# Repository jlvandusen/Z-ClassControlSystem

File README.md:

# Z-Class Control System — BB-8 firmware fleet + tooling

Firmware, build system, and a full serial mission-control CLI for the
[Z-Class BB-8 drive system](https://github.com/jlvandusen/Z-ClassDriveSystem).
**This repo is primary for all control and software supporting that drive**; the
hardware half — mechanics/STLs, PCB fabrication files, BOM, wiring docs — lives in
[Z-ClassDriveSystem](https://github.com/jlvandusen/Z-ClassDriveSystem).

VERSION 10 upcoming board

RC4 is a ground-up fix of the RC3 firmware after a 112-finding review
(110 confirmed against source): single 100 Hz PID control path with real-unit
gains, cascaded S2S position loop, servo easing on the dome tilt, non-blocking
ESP-NOW with BT-coexistence fixes, and a dozen safety/correctness repairs.
Full write-up: [`docs/BB8_RC4_Review_and_Fixes.md`](docs/BB8_RC4_Review_and_Fixes.md).

Version 9.15 working board

**RC4.7 (2026-09-01) — what it does now** (history in [`docs/CHANGELOG.md`](docs/CHANGELOG.md)):
- **Wireless console AND wireless flashing**: the dome on USB bridges `bb8` to the drive over ESP-NOW — tune with the shell closed (`bb8 monitor ball`) and update the sealed ball's firmware with `bb8 upload drive --ota` (~2–3 min, dual-slot safe).
- **Self-updating tooling**: `bb8 update` pulls from GitHub (git commits in a checkout, checksummed releases otherwise); `--flash` reflashes only boards that are behind.
- **Config as a file**: `bb8 backup` / `bb8 restore` capture and replay the drive's whole tuned state — gains, offsets, MACs, sounds, macros. `bb8 doctor` health-checks the bench in one command.
- **Black box**: a 25 Hz flight recorder freezes on safety events; `blackbox dump` explains the fall.
- **Personality**: idle chatter (`pref idle`), 4-slot action macros, dome-battery alerts, and a phone dashboard served by the dome itself (`web on` → http://192.168.4.1).
- **Live charts**: `bb8 monitor drive --web` graphs pitch/roll/pot/PWM in the browser as you tune.
- **Audio cues** (pad connect/loss, enable/disable, boot-cal) all `pref`-tunable and persisted; **dome lights** with beep-synced PSI; **dome tilt** that self-levels the dome onto the ball whenever the drive is enabled (autoBalance-independent) and tunes live with `tilt gain/lean/slew/alpha/invert` — see the [wiki](https://github.com/jlvandusen/Z-ClassControlSystem/wiki).
- **Fresh-build setup**: `cfg autocenter` drives the S2S axis to both mechanical stops and saves the midpoint as center (survives reboot, re-invocable) — hands-off S2S centering for first-time builders.

## The fleet

| Target | Board | Sketch | FQBN |
|---|---|---|---|
| `drive` | ESP32 HUZZAH32 Feather | `firmware/ESP32_DRIVE_RC4` | `esp32-bluepad32:esp32:featheresp32` |
| `body`  | Feather 32u4 | `firmware/32U4_DRIVE_RC4` | `adafruit:avr:feather32u4` |
| `imu`   | Trinket M0 + MPU6050 | `firmware/TrinketM0_MPU_RC4` | `adafruit:samd:adafruit_trinket_m0` |
| `dome`  | ESP32 HUZZAH32 Feather | `firmware/ESP32_DOME_RC4` | `esp32:esp32:featheresp32` (stock core, 3.x) |
| `ball`  | *(the dome's USB port)* | — | drive console via the dome's ESP-NOW bridge — `bb8 monitor ball` |

> **This repo's `firmware/` folder is the canonical source.** The sketches are
> plain Arduino-IDE-compatible folders — open them in the IDE from here if you
> like. RC3 originals are kept alongside for reference and rollback (point
> `targets.json` at the `_RC3` sketch and `bb8 upload`).
>
> The **drive** builds on the **Bluepad32** core (it hosts the BT gamepads).
> The **dome** builds on the **stock `esp32:esp32` core (3.x)** since RC4.4 — the
> Bluepad32 core boots a Bluetooth stack the dome never uses, which starved its
> radio into ~90 % ESP-NOW loss; the 3.x ESP-NOW callback signatures are
> version-guarded in the sketch.

**Prereqs:** [arduino-cli](https://arduino.github.io/arduino-cli/) on PATH with
cores `esp32-bluepad32:esp32` (drive), `esp32:esp32` ≥ 3.3 (dome), `adafruit:avr`, `adafruit:samd` installed, plus
the sketch libraries (SerialTransfer, DFRobotDFPlayerMini, Adafruit MPU6050,
Kalman, Adafruit NeoPixel, Servo). [.NET SDK 10+] to build the CLI.

## Install from a release — BASIC or MAX

Two installers per [release](https://github.com/jlvandusen/Z-ClassControlSystem/releases),
both no-admin, both fully self-contained:

| | **Setup-BASIC** | **Setup-MAX** |
|---|---|---|
| For | driving the droid | modifying the firmware |
| Flashing | `bb8 flash <board>` — **prebuilt binaries**, flashers bundled (esptool for the ESP32s; AVR109 and UF2 spoken natively by bb8). `bb8 upload` falls back to this automatically. | `bb8 upload <board>` — compiles from source (arduino-cli + cores, ~1 GB one-time toolchain setup) |
| Updates | `bb8 update` pulls the **latest GitHub release over HTTPS** — no git | `bb8 update` fast-forwards the git checkout — plus everything BASIC does |
| Needs | nothing but Windows | internet for the toolchain task; `git` for the source link |

Installing one over the other upgrades in place (same folder, same AppId). The zip
asset is the same bundle without an installer: extract anywhere, `.\Install-ZClass.ps1`
(add `-SkipToolchain -NoGit` for a BASIC-style setup). Cutting a release:
`tools\release\make-release.ps1 -Version X.YY` — it builds both installers.

The installed (or cloned) folder is **relocatable**: `targets.json` uses relative
`sketchRoot`/`buildRoot` paths that bb8 resolves against wherever `targets.json` lives
(found via `BB8_HOME`, the current directory and its parents, or next to `bb8.exe`).

**New droid or fresh board set?** Follow
[`docs/FirstTimeSetup.md`](docs/FirstTimeSetup.md) — flash order, radio-MAC pairing,
controller pairing, first calibration, and the polarity checks that must come before
the first enable.

## bb8 Commander

```powershell
.\install.ps1          # one-time: builds bin\bb8.exe (bb8.cmd wraps it)

bb8 list               # targets + detected USB serial ports
bb8 build all          # compile the whole fleet
bb8 upload drive       # compile + flash (auto-detects the port)
bb8 upload drive --ota # flash the DRIVE wirelessly through the dome (sealed shell)
bb8 flash drive        # flash the PREBUILT release binary — no compiler, no cores, no git
bb8 deploy drive       # build + upload + open monitor
bb8 doctor             # health check: environment, boards, firmware freshness
bb8 backup             # capture the drive's tuned config to a replayable file
bb8 restore <file>     # ...and put it back (board swaps keep the tune)
bb8 identify           # probe every port, read boot banners
bb8 update             # pull new firmware / tooling from GitHub
bb8 update --flash     # ...and reflash every plugged-in board that is behind its sketch
bb8 monitor ball       # drive console THROUGH the dome over ESP-NOW (shell closed)
bb8 monitor drive --web    # + live telemetry charts at http://127.0.0.1:8787
bb8 tune s2s --port COMx   # live tuner — works through the bridge too (COMx = dome)
```

### Staying current with GitHub

Two channels, picked automatically by whether the folder is a git checkout:

- **Git checkout (MAX / dev):** every `build` / `upload` / `deploy` (and any other
  command, at most once every 4 h) does a `git fetch` first and **fast-forwards the
  checkout when that is safe** — it never touches local commits or edits (the only
  files it sets aside are the generated `versions.json` / `BuildStamp.h`, keeping the
  higher build counters). If `tools/Bb8Commander` changed, `bb8.cmd` rebuilds
  `bin\bb8.exe` and re-runs your command. `bb8 update --flash` reads each plugged-in
  board's banner (`git HASH`) and reflashes only the boards whose sketch has commits
  since that hash.
- **No git (BASIC):** `bb8 update` finds the **latest GitHub release over plain
  HTTPS** (no git, no API key), downloads it, and applies it over the install —
  including a new `bb8.exe`, which swaps itself in on the next run. `bb8 update
  --flash` then compares each plugged-in board's banner build number against the
  release's prebuilt binaries and runs `bb8 flash` on the ones that are behind.

Offline, either channel says so once and carries on with what's on disk.
Skip the check with `--no-update` or `BB8_NO_UPDATE=1`.

### The serial monitor

```powershell
bb8 monitor drive                       # one board
bb8 monitor drive body --log run1.csv   # several boards at once, CSV log
bb8 monitor COM7 --baud 115200          # raw port
```

Full-screen with a **pinned input line** — incoming traffic scrolls above it and
never clobbers what you're typing:

| Key | Action |
|---|---|
| type + `Enter` | send a serial command to the **active** board (`help`, `pid show`, `telemetry on`, `debug s2s`, …) |
| `↑` / `↓` | command history |
| `Tab` | switch active board (multi-board mode; each board's lines are color-tagged) |
| `Esc` / `Ctrl+C` | exit |

Send `telemetry on` to the drive and the 20 Hz stream renders as a **live
status bar** (pitch/roll/pot/target/PWM/loop-Hz) instead of scrolling spam —
add `--show-tlm` to scroll it too. `--log file.csv` captures *everything*
(timestamp, board, line — telemetry included) for offline plotting.
`--raw` disables the UI for piping.

Boards reset or unplugged mid-session **auto-reconnect**. Note: close the
monitor before `bb8 upload` on the same port — two programs can't hold one COM
port.

Port auto-detection: 32u4 and Trinket by USB VID/PID; the two ESP32s share the
same CP2104 bridge, so the tool resets the board and matches its boot banner.
If that fails, pass `--port COMx`.

### Typical tuning session

```
bb8 monitor drive --log tune1.csv
> telemetry on
> pid show
> pid set drive kp 14
> pid save
```

Tuning procedure + starting gains: [`docs/BB8_RC4_Review_and_Fixes.md`](docs/BB8_RC4_Review_and_Fixes.md) §5.

### Rig experiments — let the droid tune itself (roller cradle)

With the ball on the roller cradle (free to pitch/roll in place), the firmware
can measure its own physics. In the monitor, with drive enabled:

```
> telemetry fast              # 100 Hz capture for clean data
> autotune drive              # relay autotune: a small controlled rock,
                              #   measures Ku/Tu, prints suggested Kp/Ki/Kd
> autotune apply              # take the suggestion (then 'pid save')
> autotune s2s                # same for the roll/S2S loop
> step drive 80 2000          # open-loop step for system ID captures
> step s2s 200 2000
```

Safety: experiments require drive enabled, abort on |angle| > 15°, joystick
grab, mode change, or 25 s timeout. If the relay oscillation runs away instead
of settling, your plant sign is inverted — rerun with a negative amplitude
(`autotune drive -60`).

Then analyze any logged session offline:

```
bb8 analyze tune1.csv
```

Reports per-axis bias/noise/oscillation frequency, PWM saturation, S2S
tracking error, and concrete gain prescriptions. For a deeper read, hand the
CSV to Claude in this workspace.

## Layout

```
firmware/            Arduino sketches — RC4 (current) + RC3 (reference/rollback)
tools/Bb8Commander/  C#/.NET 10 source for the bb8 CLI
targets.json         fleet definition (sketch, FQBN, VID/PID, boot banner)
docs/                full review, fixes, tuning guide, way forward
install.ps1          builds bin\bb8.exe
bb8.cmd              command wrapper (also rebuilds bin\ after a pulled tool change)
```

## Why the firmware is C++ and the tooling is C#

The firmware depends on Bluepad32 (BT-Classic gamepad host), ESP-NOW, and a
100 Hz control loop — none of which exist in .NET nanoFramework, and the 32u4
(2.5 KB RAM) and SAMD21 can't host a runtime at all. Going full C# would mean
new hardware, new controller input, and worse latency for zero functional gain.
The PC side is the opposite story — everything above the serial port is C#.

## Branches

| Branch | Hardware | Purpose |
|---|---|---|
| `main` | **v9.15 / v8.2 boards** (HUZZAH32, Feather 32u4, Trinket M0) | RC4.x firmware, bb8 tooling, runbook — the droid as built today. Keeps getting fixes. |
| `v10` | **v10.0 boards** (ESP32 DevKit, RP2350-Zero, ICM-42688 IMU) | New firmware ports (`RP2350_BODY_RC5`, drive IMU module, new pin tables), `targets.json` for the new modules, KiCad sources under `hardware/`. |

bb8 Commander and the docs are shared: fix them on `main`, merge `main` into `v10` regularly (`git checkout v10 && git merge main`). Firmware directories diverge by design.

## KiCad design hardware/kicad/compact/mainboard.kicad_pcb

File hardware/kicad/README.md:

# KiCad project — Z-Class v10 mainboard (generated)

Generated by `tools/hw/gen_kicad.py` from `hardware/netlist/mainboard.py` — edit the netlist, re-run,
don't hand-edit the generated files until layout work starts (then the netlist becomes the record and
the .kicad_pcb the working file).

```
py tools/hw/gen_kicad.py hardware/netlist/mainboard.py hardware/kicad/extended/mainboard
```

| File | Content |
|---|---|
| `mainboard.kicad_pro/.kicad_sch/.kicad_pcb` | project · schematic (label-connected, one symbol per part) · PCB |
| `board_outline_draft.dxf` | casing inner wall inset 1.5 mm — already on Edge.Cuts; true-offset it in KiCad before fab |
| `casing_inner_wall.dxf`, `casing_outer_wall.dxf` | reference contours (User.Comments) |

PCB coordinates: the **axle centre is at (150, 150) mm** in KiCad; +x toward the tail, +y up in the
netlist = down in KiCad (handled by the generator). Edge.Cuts includes the Ø 38 axle cut-out.
Netclasses come from the netlist (Default 0.15 mm clearance / 0.25 mm track, Rail 0.6, Motor 0.5,
Audio 1.0, Power 1.2). Routing recipe: `tools/hw/prep_route.py --route-5v` → Freerouting
(`tools/freerouting/`, `-mp 16 -mt 6`) → `tools/hw/post_route.py` (SES import + GND stitching), last
nets by hand in pcbnew. KiCad DRC is the judge — Freerouting's on-screen "violations" count is not.

## Two board variants (Aug 2026)

| Folder | Outline | Use |
|---|---|---|
| `extended/` | teardrop 152 × 125 mm — casing extended 15 mm downward | the roomier layout; auto-placed |
| `compact/`  | teardrop 152 × 110 mm — the original casing | **the built board**: hand-placed (James), 4-layer routed, DRC 0 errors, JLCPCB package r7 (`hardware/fab/`) |

Both are generated from the **same netlist** (`hardware/netlist/mainboard.py`) and are kept in sync
with `tools/hw/sync_parts.py <hand-placed.kicad_pcb> <freshly-generated.kicad_pcb>` — it updates
parts/nets/footprints and never moves anything. Regenerate with
`py tools/hw/gen_kicad.py hardware/netlist/mainboard.py hardware/kicad/<variant>/mainboard`
(the outline is read from `<variant>/board_outline_draft.dxf`). Fab package:
`.\tools\hw\fab_outputs.ps1 compact` (or `extended`) → `hardware/fab/<variant>-<date>/`.

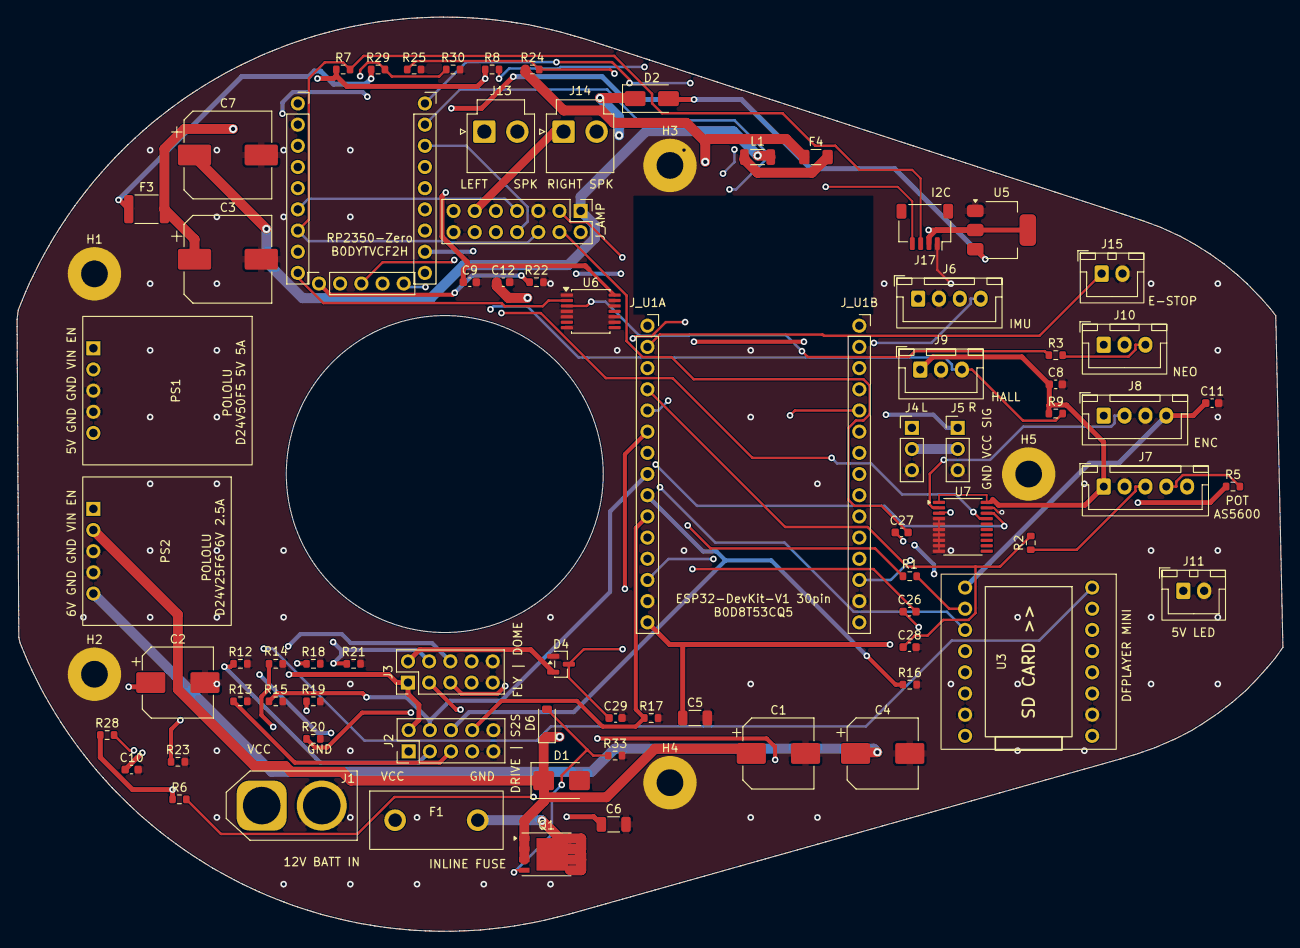
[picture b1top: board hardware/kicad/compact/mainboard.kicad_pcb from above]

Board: 4 copper layers, 151.8 x 109.6 mm, 83 parts (0 on the bottom side), 58 nets.

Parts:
C1: 220u/25V; CP_Elec_8x10
C2: 470u/10V; CP_Elec_8x10
C3: 1000u/10V; CP_Elec_10x10
C4: 470u/16V; CP_Elec_8x10
C5, C6: 10u; C_1206_3216Metric
C7: 1000u/25V; CP_Elec_10x10
C8, C9, C10, C11, C12, C28, C29: 100n; C_0603_1608Metric
C26, C27: 1u; C_0603_1608Metric
D1: SMBJ15A; D_SMB
D2: SS14; D_SMA
D4: BAT54S; SOT-23
D6: BZT52C12 12V zener; D_SOD-123
F1: 10A blade fuse; Fuse_Mini_Blade
F3: 3A polyfuse; Fuse_1812_4532Metric
F4: 3A fuse; Fuse_1206_3216Metric
H1, H2, H3, H4, H5: M3 boss; MountingHole_3.2mm_M3_Pad
J1: XT60PB-M vertical; AMASS_XT60-M_1x02_P7.20mm_Vertical
J2, J3: DFR0601 ribbon 2x5; PinHeader_2x05_P2.54mm_Vertical
J4: Servo L; PinHeader_1x03_P2.54mm_Vertical
J5: Servo R; PinHeader_1x03_P2.54mm_Vertical
J6: IMU BMI160 I2C; JST_XH_B4B-XH-A_1x04_P2.50mm_Vertical
J7: S2S AS5600/pot; JST_XH_B5B-XH-A_1x05_P2.50mm_Vertical
J8: Dome encoder; JST_XH_B4B-XH-A_1x04_P2.50mm_Vertical
J9: Hall; JST_XH_B3B-XH-A_1x03_P2.50mm_Vertical
J10: Body NeoPixel; JST_XH_B3B-XH-A_1x03_P2.50mm_Vertical
J11: Slip ring (body lights); JST_XH_B2B-XH-A_1x02_P2.50mm_Vertical
J13: SPK L; JST_VH_B2P-VH_1x02_P3.96mm_Vertical
J14: SPK R; JST_VH_B2P-VH_1x02_P3.96mm_Vertical
J15: ESTOP; JST_XH_B2B-XH-A_1x02_P2.50mm_Vertical
J17: I2C-B exp (RP2350); JST_SH_SM04B-SRSS-TB_1x04-1MP_P1.00mm_Horizontal
J_AMP: MAX9744 amp module hdr; PinHeader_2x07_P2.54mm_Vertical
J_U1A: ESP32 DevKitC socket L (1x15); PinSocket_1x15_P2.54mm_Vertical
J_U1B: ESP32 DevKitC socket R (1x15); PinSocket_1x15_P2.54mm_Vertical
J_U2A: RP2350-Zero socket L (1x9); PinSocket_1x09_P2.54mm_Vertical
J_U2B: RP2350-Zero socket R (1x9); PinSocket_1x09_P2.54mm_Vertical
J_U2C: RP2350-Zero socket end (1x5); PinSocket_1x05_P2.54mm_Vertical
L1: FB 600R 3A; L_1206_3216Metric
PS1: Pololu D24V50F5 5V 5A; Pololu_D24V50F5
PS2: Pololu D24V25F6 6V 2.5A; Pololu_D24V25F6
Q1: Si7461DP P-FET RPP; PowerPAK_SO-8_Single
R1, R2: 1k; R_0603_1608Metric
R3: 330R; R_0603_1608Metric
R5, R6, R7, R8: 4.7k; R_0603_1608Metric
R9, R12, R13, R14, R15, R16, R17, R18, R19, R20, R21, R22, R23, R25, R28, R29, R30: 10k; R_0603_1608Metric
R24, R33: 47k; R_0603_1608Metric
U3: DFPlayer Mini; DFPlayer_2x8
U5: AP7361C-33 3.3V LDO; SOT-223-3_TabPin2
U6: 74AHCT125; TSSOP-14_4.4x5mm_P0.65mm
U7: 74LVC245A; TSSOP-20_4.4x6.5mm_P0.65mm

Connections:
+3V3: C6.1, C8.1, D4.2, J2.1, J2.2, J3.1, J3.2, J7.1, J9.1, J17.2, J_AMP.13, R5.1, R6.1, R7.1, R8.1, R9.1, R28.1, U5.2, U7.1, U7.20
+5V_LED: C3.1, F3.2, J10.1, J11.1
+5V_LOGIC: C2.1, C5.1, C9.1, C10.1, C11.1, D2.2, F3.1, J6.1, J8.4, J_U1A.15, PS1.5, R29.1, U3.1, U5.3, U6.14
+6V_SERVO: C4.1, J4.2, J5.2, PS2.5
AMP_12V: C7.1, J_AMP.1, L1.2
AMP_12V_F: F4.2, L1.1
AMP_INL: C26.2, J_AMP.3
AMP_INR: C27.2, J_AMP.4
AMP_SHDN: J_AMP.8, J_U2B.3
BAT+: F1.1, J1.1
BAT_F: F1.2, Q1.5
DF_BUSY: J_U2A.8, U3.16
DF_DAC_L: C26.1, U3.5
DF_DAC_R: C27.1, U3.4
DF_RX_MOD: R1.2, U3.2
DF_RX_RP: J_U2B.6, U3.3
DF_TX_RP: J_U2B.5, R1.1
DOME_INA: J3.6, J_U2C.1, R22.1
DOME_INB: J3.8, J_U2C.2, R23.1
DOME_PWM: J3.4, J_U2B.9, R21.1
DRIVE_INA: J2.5, J_U1B.10, R13.1
DRIVE_INB: J2.7, J_U1B.9, R14.1
DRIVE_PWM: J2.3, J_U1B.11, R12.1
ENC_A_3V3: J_U2C.3, U7.18
ENC_A_5V: J8.2, U7.2
ENC_B_3V3: J_U2C.4, U7.17
ENC_B_5V: J8.1, U7.3
ESTOP_SENSE: J15.1, J_U1A.2, R28.2
FLY_INA: J3.5, J_U1A.7, R19.1
FLY_INB: J3.7, J_U1A.11, R20.1
FLY_PWM: J3.3, J_U1A.6, R18.1
GND: C1.2, C2.2, C3.2, C4.2, C5.2, C6.2, C7.2, C8.2, C9.2, C10.2, C11.2, C12.2, C28.2, C29.2, D1.2, D4.1, H1.1, H2.1, H3.1, H4.1, H5.1, J1.2, J2.9, J2.10, J3.9, J3.10, J4.3, J5.3, J6.2, J7.2, J8.3, J9.2, J10.2, J11.2, J15.2, J17.1, J_AMP.2, J_AMP.5, J_AMP.14, J_U1A.14, J_U1B.14, J_U2A.2, PS1.3, PS1.4, PS2.3, PS2.4, R12.2, R13.2, R14.2, R15.2, R16.2, R17.2, R18.2, R19.2, R20.2, R21.2, R22.2, R23.2, R25.2, R30.2, R33.2, U3.7, U3.10, U5.1, U6.1, U6.4, U6.5, U6.7, U6.9, U6.10, U6.12, U6.13, U7.4, U7.5, U7.6, U7.7, U7.8, U7.9, U7.10, U7.19
HALL: J9.3, J_U2C.5, R9.2
I2C_A_SCL: J6.3, J7.5, J_U1B.13, R6.2
I2C_A_SDA: J6.4, J7.4, J_U1A.13, R5.2
I2C_B_SCL: J17.4, J_AMP.7, J_U2A.6, R8.2
I2C_B_SDA: J17.3, J_AMP.6, J_U2A.7, R7.2
LINK_ESP_TX: J_U1B.5, J_U2B.2
LINK_RP_TX: J_U1B.2, J_U2B.1
NEO_3V3: J_U2A.9, U6.2
NEO_5V: R3.1, U6.3
NEO_OUT: J10.3, R3.2
Q1_G: D6.2, Q1.4, R33.1
RP_5V: C12.1, D2.1, J_U2A.1
S2S_INA: J2.6, J_U1A.9, R16.1
S2S_INB: J2.8, J_U1A.10, R17.1
S2S_OUT: J7.3, R2.1
S2S_POS: C28.1, J_U1A.4, R2.2
S2S_PWM: J2.4, J_U1A.8, R15.1
SERVO_L: J4.1, J_U2B.7
SERVO_R: J5.1, J_U2B.8
SPK_L+: J13.1, J_AMP.9
SPK_L-: J13.2, J_AMP.10
SPK_R+: J14.1, J_AMP.11
SPK_R-: J14.2, J_AMP.12
V5_SENSE: J_U2A.5, R29.2, R30.1
VBAT_SENSE: C29.1, D4.3, J_U1A.5, R24.2, R25.1
VIN: C1.1, D1.1, D6.1, F4.1, PS1.2, PS2.2, Q1.1, Q1.2, Q1.3, R24.1

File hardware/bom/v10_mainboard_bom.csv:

Ref,Qty,Value / Part,MPN,Package,Supplier,Notes
U1,1,ESP-WROOM-32 DevKit (ELEGOO) - CUSTOMER FITS into J_U1A/J_U1B,ESP32-DevKit-V1 30-pin,plugs into 2x 1x15 sockets,Amazon B0D8T53CQ5,Drive MCU; 30-pin ONLY (38-pin is wider); antenna end toward H3
U2,1,Waveshare RP2350-Zero - CUSTOMER FITS into J_U2A/B/C,RP2350-Zero,plugs into 2x 1x9 + 1x5 sockets,Amazon B0DYTVCF2H,Body co-processor
U3,1,DFPlayer Mini,DFR0299,2x8 0.1in,DFRobot / AliExpress,SD MP3 source; socket
(module),1,MAX9744 class-D amp MODULE - CUSTOMER FITS on J_AMP,Adafruit 1752 (MAX9744 20W stereo I2C),plugs into J_AMP 2x7 harness,Adafruit / Digi-Key,2x20W I2C volume at 0x4B; rev A uses the module - the on-board TQFN (U4) is deferred to rev B
U5,1,3.3V 1A LDO,AMS1117-3.3,SOT-223,LCSC C6186,Pinout GND/OUT(tab)/IN as routed. Alt AP7361C-33ER-13 (SOT-223R, C3743528). NOT AP7361C-33E-13 (IN/GND/OUT - wrong for this board)
U6,1,NeoPixel level shifter,74AHCT125PW,TSSOP-14,Digi-Key,3.3->5V WS2812 data
U7,1,Encoder level shifter,74LVC245APW,TSSOP-20,Digi-Key,5V encoder A/B (A1/A2) -> 3.3V (B1/B2); DIR (pin 1) = +3V3 for A->B (r7 gerbers; on r6 boards cut the GND spoke into pin 1 and bridge pin 1 to pin 20); unused A3-A8 tied to GND
PS1,1,5V 5A buck module,Pololu D24V50F5,Pololu 5-pin row EN VIN GND GND OUT,Pololu 2851,+5V_LOGIC and +5V_LED
PS2,1,6V 2.5A buck module,Pololu D24V25F6,Pololu 5-pin row EN VIN GND GND OUT,Pololu 2852,+6V_SERVO: 6.0 V suits BOTH Hitec HS-805BB (4.8-6V) and JX PDI-HV2060MG (6-8.4V)
Q1,1,P-FET reverse polarity (high-side RPP),SI7461DP-T1-GE3,PowerPAK SO-8,Digi-Key,"-60V 14.5mOhm -14A; pads 1-3 S=VIN, 4 G, 5 tab D=BAT_F"
D1,1,TVS,SMBJ15A,SMB,Digi-Key,Input clamp 12V pack
D2,1,Schottky,SS14,SMA,Digi-Key,+5V_LOGIC -> RP2350-Zero 5V (USB back-feed block); pad1 K = RP_5V
D6,1,Zener 12V (Q1 gate clamp),BZT52C12-7-F,SOD-123,Digi-Key,VGS clamp S->G
D4,1,BAT54S,BAT54S,SOT-23,Digi-Key,ADC clamp on VBAT_SENSE (GPIO35); pin1 A->GND pin2 K->3V3 pin3 COM->sense
F1,1,Mini blade fuse holder + 10A ATM fuse,Keystone 3568 / 10A ATM,THT 9.9mm pitch,LCSC C5249699 / auto store,Board input (bucks + amp only; motors fed from the pack directly)
F3,1,Polyfuse 3A,MF-MSMF300,1812,Digi-Key,+5V_LED to slip ring
F4,1,Fuse 3A fast (amp 12V),0466003.NR,1206,Digi-Key,Littelfuse 466 series 32V
L1,1,Ferrite bead 600R@100MHz 2.9A,BLM31KN601SN1L,1206,LCSC C668306,Amp supply (PG variant is only 1.5 A)
C1,1,220uF 25V electrolytic,EEE-FK1E221P,SMD 8x10,Digi-Key,VIN
C2,1,470uF 10V,EEE-FK1A471P,SMD 8x10,Digi-Key,+5V_LOGIC
C3,1,1000uF 10V,EEE-FK1A102P,SMD 10x10,Digi-Key,+5V_LED
C4,1,470uF 16V,EEE-FK1C471P,SMD 8x10,Digi-Key,+6V_SERVO
C7,1,1000uF 25V,EEE-FP1E102AP,SMD 10x10.2,Digi-Key,MAX9744 supply (10mm can to match CP_Elec_10x10; verify height vs casing)
C5-C6,2,10uF 25V X7R,GRM31CR71E106KA12L,1206,Digi-Key,Rail local (+5V_LOGIC / +3V3)
C8-C12 + C29,6,100nF 50V X7R,CL10B104KB8NNNC,0603,Digi-Key,Decoupling: C8 U7 / C9 U6 / C10-C11 +5V_LOGIC at the modules / C12 RP_5V; C29 = VBAT_SENSE ADC reservoir
C26-C27,2,1uF 16V X7R,CL10B105KO8NNNC,0603,Digi-Key,Audio input coupling
C28,1,100nF,CL10B104KB8NNNC,0603,Digi-Key,Pot / AS5600 OUT filter
R1,1,1k 1%,RC0603FR-071KL,0603,Digi-Key,DFPlayer TX series
R2,1,1k 1%,RC0603FR-071KL,0603,Digi-Key,Pot/AS5600 OUT series
R3,1,330R 1%,RC0603FR-07330RL,0603,Digi-Key,NeoPixel data series (body)
R5-R8,4,4.7k 1%,RC0603FR-074K7L,0603,Digi-Key,I2C pull-ups (R5/R6 ESP32 bus I2C-A; R7/R8 RP2350 bus I2C-B)
R9,1,10k 1%,RC0603FR-0710KL,0603,Digi-Key,Hall pull-up (encoder A/B need none - driven through U7)
R12-R23,12,10k 1%,RC0603FR-0710KL,0603,Digi-Key,Motor driver PWM/INA/INB pull-downs (4 ch x 3)
R24,1,47k 1%,RC0603FR-0747KL,0603,Digi-Key,Battery sense top
R25,1,10k 1%,RC0603FR-0710KL,0603,Digi-Key,Battery sense bottom
R28,1,10k 1%,RC0603FR-0710KL,0603,Digi-Key,ESTOP pull-up
R29-R30,2,10k 1%,RC0603FR-0710KL,0603,Digi-Key,+5V_LOGIC sense divider (RP2350 GP28)
R33,1,47k 1%,RC0603FR-0747KL,0603,Digi-Key,Q1 gate pull-down
J1,1,XT60 male PCB VERTICAL,XT60PB-M (Amass),THT 2x dia4.0 @ 7.2mm,LCSC C19268037 (alt JLC lib C9900017179),SINGLE board VCC input: 12 V 3S4P pack (9-12.6 V) -> F1 10A -> Q1 RPP -> VIN; pack lead = XT60 female
J_AMP,1,Pin header 2x7 0.1in male,PH2-14-UA,TH,Digi-Key,MAX9744 amp module harness: 1 VDD12 2 GND 3 INL 4 INR 5 AGND 6 SDA 7 SCL 8 SHDN 9-12 SPK L+/L-/R+/R- 13 Vi2c(3V3) 14 GND
J_U1A-J_U1B,2,Female header 1x15 2.54mm 8.5mm,B-2200S15P-A120 (Ckmtw),THT,LCSC C124408,ESP32 DevKitC sockets
J_U2A-J_U2B,2,Female header 1x9 2.54mm 8.5mm,B-2200S09P-A120 (Ckmtw),THT,LCSC C124417,RP2350-Zero side sockets (low stock: cut a 1x15 if out)
J_U2C,1,Female header 1x5 2.54mm 8.5mm,2.54-1*5P (BOOMELE),THT,LCSC C50950,RP2350-Zero end socket
J2-J3,2,Pin header 2x5 0.1in male (no shroud),PH2-10-UA,TH,Digi-Key,Motor driver IDC ribbons - odd pins = channel A row (VCC PWM INA INB GND); even = channel B
J4-J5,2,Pin header 1x3 0.1in,PH1-03-UA,TH,Digi-Key,Servos L / R (SIG +6V GND) - Hitec HS-805BB or JX PDI-HV2060MG jumbo servos
J6,1,JST-XH 4-pin,B4B-XH-A,XH TH,Digi-Key,IMU GY-BMI160 over I2C: 1 +5V->VIN, 2 GND, 3 SCL, 4 SDA (same order as v9.15 MPU)
J7,1,JST-XH 5-pin,B5B-XH-A,XH TH,Digi-Key,S2S sensor (3V3 GND OUT SDA SCL) - AS5600 or pot
J8,1,JST-XH 4-pin,B4B-XH-A,XH TH,Digi-Key,Dome encoder (B A GND 5V) - same order as v9.15 DOME_ENC
J9,1,JST-XH 3-pin,B3B-XH-A,XH TH,Digi-Key,Hall
J10,1,JST-XH 3-pin,B3B-XH-A,XH TH,Digi-Key,Body NeoPixel (5V GND DATA)
J11,1,JST-XH 2-pin,B2B-XH-A,XH TH,Digi-Key,Slip ring: +5V_LED / GND to body-shell NeoPixels (pack charges via its own lead - no charge path on board)
J13-J14,2,JST-VH 2-pin,B2P-VH,VH TH,Digi-Key,Speakers L / R (BTL)
J15,1,JST-XH 2-pin,B2B-XH-A,XH TH,Digi-Key,ESTOP loop
J17,1,JST-SH 4-pin (Qwiic),SM04B-SRSS-TB,SH SMD,Digi-Key,I2C expansion on the RP2350 bus (ESP32 bus is on J7 pins 4/5)
H1-H5,5,M3 mounting holes (plated; GND ring),-,3.2mm,-,"board (x,y) from the axle centre: H1 (-42,24) H2 (-42,-24) H3 (27,37) H4 (27,-37) H5 (70,0) - see hardware/mechanical/compact-cover/cover_layout.md"
PCB,1,4-layer 1oz 1.6mm FR4 (F / In1 GND / In2 +5V pour + signal / B),-,-,JLCPCB (fab package hardware/fab/ZDrive_v10_compact_JLCPCB_r7.zip),teardrop ~152x110 compact (ordered rev A); ~152x125 extended variant unrouted. No test points, no reset switch and no MOTOR_EN gate on rev A

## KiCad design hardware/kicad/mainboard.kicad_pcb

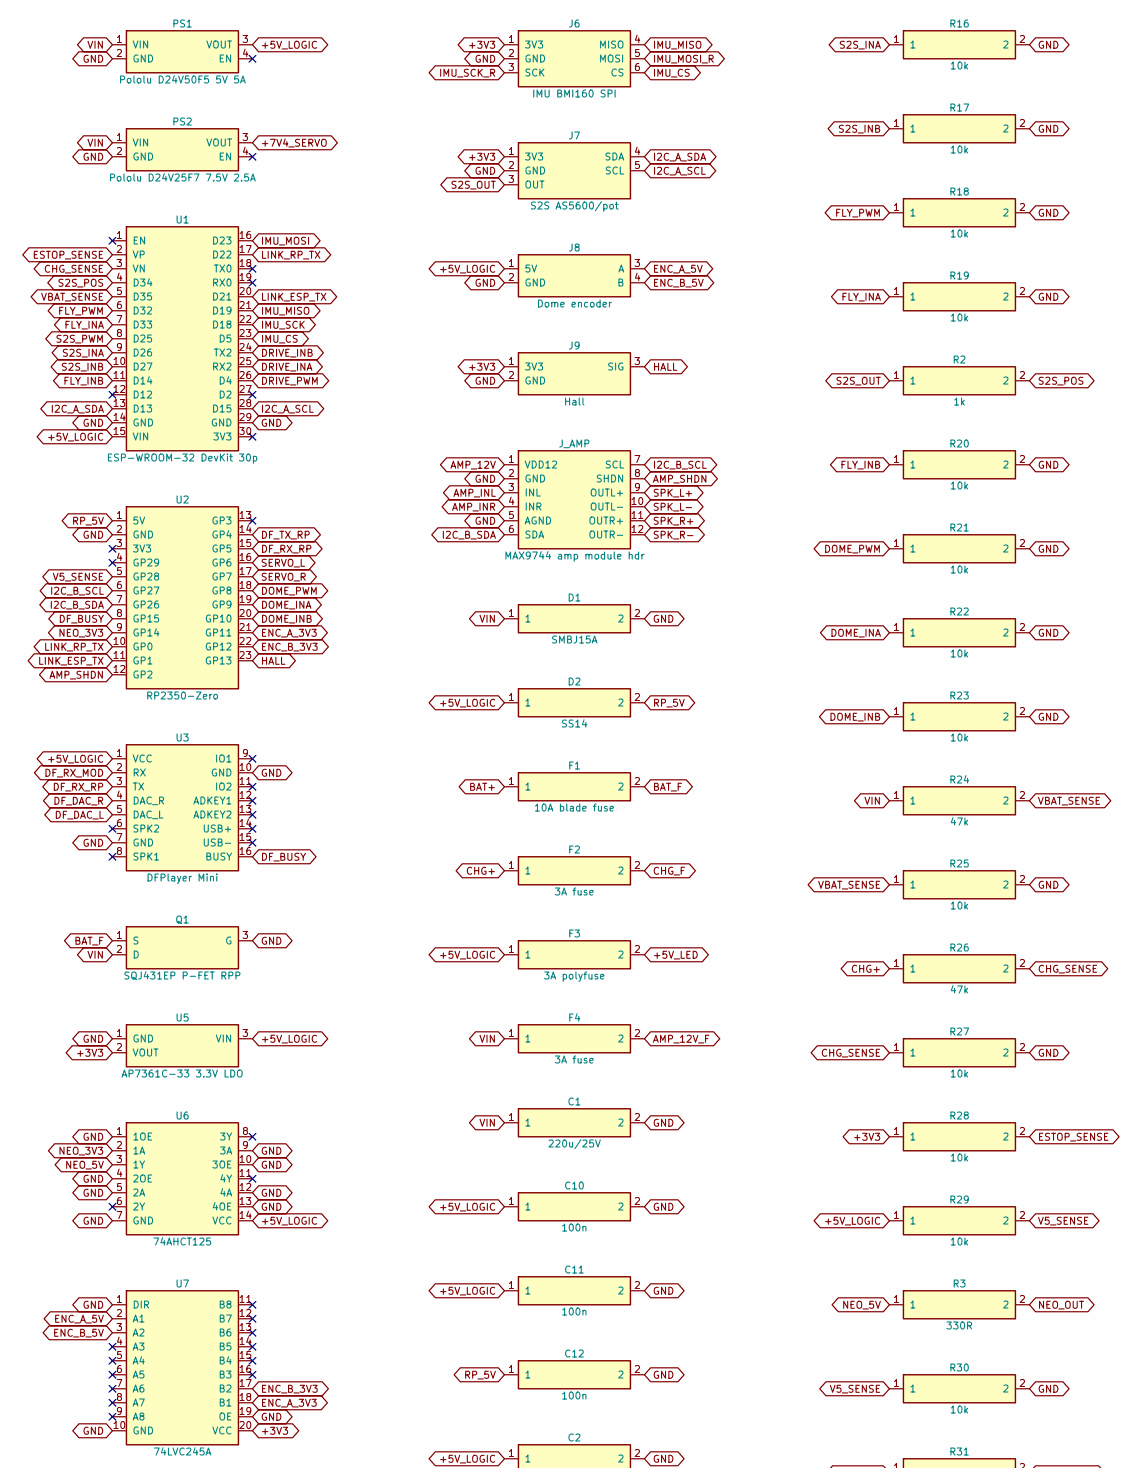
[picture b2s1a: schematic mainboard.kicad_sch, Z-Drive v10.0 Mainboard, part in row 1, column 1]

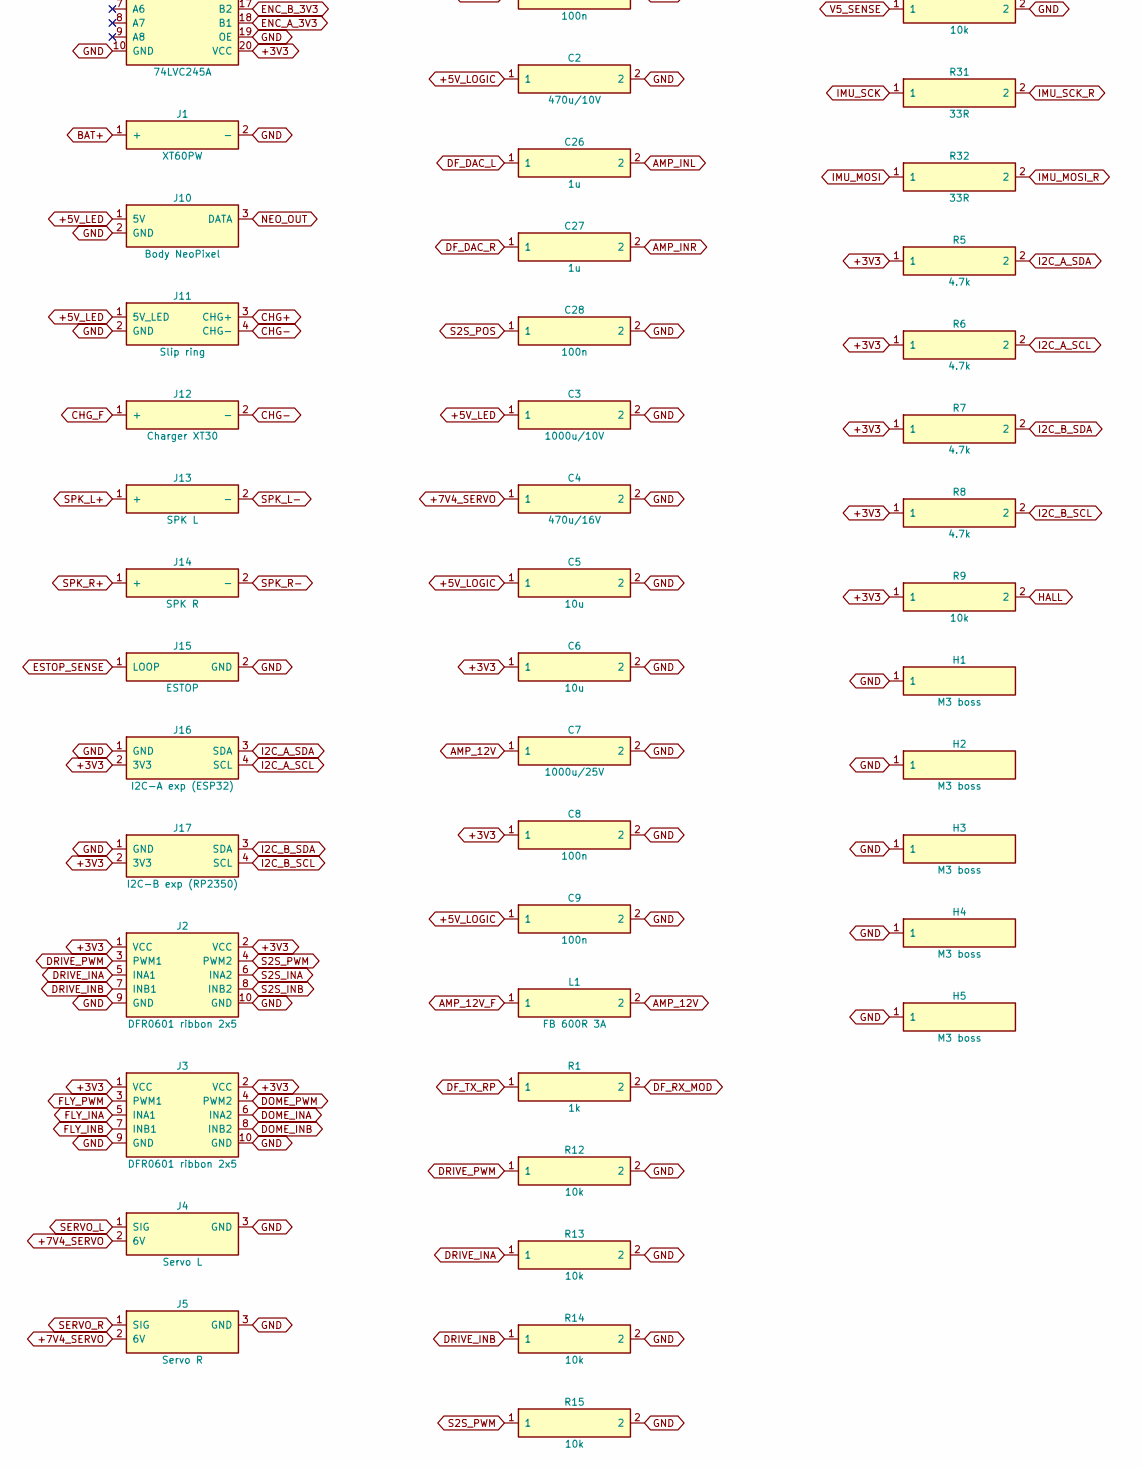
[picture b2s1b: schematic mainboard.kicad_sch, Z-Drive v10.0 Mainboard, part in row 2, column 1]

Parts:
C1: 220u/25V; CP_Elec_8x10
C2: 470u/10V; CP_Elec_8x10
C3: 1000u/10V; CP_Elec_10x10
C4: 470u/16V; CP_Elec_8x10
C5, C6: 10u; C_1206_3216Metric
C7: 1000u/25V; CP_Elec_10x10
C8, C9, C10, C11, C12, C28: 100n; C_0603_1608Metric
C26, C27: 1u; C_0603_1608Metric
D1: SMBJ15A; D_SMB
D2: SS14; D_SMA
F1: 10A blade fuse; Fuse_Mini_Blade
F2, F4: 3A fuse; Fuse_1206_3216Metric
F3: 3A polyfuse; Fuse_1812_4532Metric
H1, H2, H3, H4, H5: M3 boss; MountingHole_3.2mm_M3_Pad
J1: XT60PW
J2, J3: DFR0601 ribbon 2x5; Hdr_2x5_shrouded
J4: Servo L; JST_XH_B3B-XH-A_1x03_P2.50mm_Vertical
J5: Servo R; JST_XH_B3B-XH-A_1x03_P2.50mm_Vertical
J6: IMU BMI160 SPI; JST_SH_SM06B-SRSS-TB_1x06-1MP_P1.00mm_Horizontal
J7: S2S AS5600/pot; JST_XH_B5B-XH-A_1x05_P2.50mm_Vertical
J8: Dome encoder; JST_XH_B4B-XH-A_1x04_P2.50mm_Vertical
J9: Hall; JST_XH_B3B-XH-A_1x03_P2.50mm_Vertical
J10: Body NeoPixel; JST_XH_B3B-XH-A_1x03_P2.50mm_Vertical
J11: Slip ring; JST_VH_B4P-VH_1x04_P3.96mm_Vertical
J12: Charger XT30; XT30PW
J13: SPK L; JST_VH_B2P-VH_1x02_P3.96mm_Vertical
J14: SPK R; JST_VH_B2P-VH_1x02_P3.96mm_Vertical
J15: ESTOP; JST_XH_B2B-XH-A_1x02_P2.50mm_Vertical
J16: I2C-A exp (ESP32); JST_SH_SM04B-SRSS-TB_1x04-1MP_P1.00mm_Horizontal
J17: I2C-B exp (RP2350); JST_SH_SM04B-SRSS-TB_1x04-1MP_P1.00mm_Horizontal
J_AMP: MAX9744 amp module hdr; Hdr_2x6
L1: FB 600R 3A; L_1206_3216Metric
PS1: Pololu D24V50F5 5V 5A; Pololu_D24V50F5
PS2: Pololu D24V25F7 7.5V 2.5A; Pololu_D24V22F6
Q1: SQJ431EP P-FET RPP; PowerPAK_SO-8_Single
R1, R2: 1k; R_0603_1608Metric
R3: 330R; R_0603_1608Metric
R5, R6, R7, R8: 4.7k; R_0603_1608Metric
R9, R12, R13, R14, R15, R16, R17, R18, R19, R20, R21, R22, R23, R25, R27, R28, R29, R30: 10k; R_0603_1608Metric
R24, R26: 47k; R_0603_1608Metric
R31, R32: 33R; R_0603_1608Metric
U1: ESP-WROOM-32 DevKit 30p; DevKit_2x15_25.4mm
U2: RP2350-Zero; RP2350_Zero
U3: DFPlayer Mini; DFPlayer_2x8
U5: AP7361C-33 3.3V LDO; SOT-223-3_TabPin2
U6: 74AHCT125; TSSOP-14_4.4x5mm_P0.65mm
U7: 74LVC245A; TSSOP-20_4.4x6.5mm_P0.65mm

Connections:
+3V3: C6.1, C8.1, J2.1 (VCC), J2.2 (VCC), J3.1 (VCC), J3.2 (VCC), J6.1 (3V3), J7.1 (3V3), J9.1 (3V3), J16.2 (3V3), J17.2 (3V3), R5.1, R6.1, R7.1, R8.1, R9.1, R28.1, U5.2 (VOUT), U7.20 (VCC)
+5V_LED: C3.1, F3.2, J10.1 (5V), J11.1 (5V_LED)
+5V_LOGIC: C2.1, C5.1, C9.1, C10.1, C11.1, D2.1, F3.1, J8.1 (5V), PS1.3 (VOUT), R29.1, U1.15 (VIN), U3.1 (VCC), U5.3 (VIN), U6.14 (VCC)
+7V4_SERVO: C4.1, J4.2 (6V), J5.2 (6V), PS2.3 (VOUT)
AMP_12V: C7.1, J_AMP.1 (VDD12), L1.2
AMP_12V_F: F4.2, L1.1
AMP_INL: C26.2, J_AMP.3 (INL)
AMP_INR: C27.2, J_AMP.4 (INR)
AMP_SHDN: J_AMP.8 (SHDN), U2.12 (GP2)
BAT+: F1.1, J1.1 (+)
BAT_F: F1.2, Q1.1 (S)
CHG+: F2.1, J11.3 (CHG+), R26.1
CHG-: J11.4 (CHG-), J12.2 (-)
CHG_F: F2.2, J12.1 (+)
CHG_SENSE: R26.2, R27.1, U1.3 (VN)
DF_BUSY: U2.8 (GP15), U3.16 (BUSY)
DF_DAC_L: C26.1, U3.5 (DAC_L)
DF_DAC_R: C27.1, U3.4 (DAC_R)
DF_RX_MOD: R1.2, U3.2 (RX)
DF_RX_RP: U2.15 (GP5), U3.3 (TX)
DF_TX_RP: R1.1, U2.14 (GP4)
DOME_INA: J3.6 (INA2), R22.1, U2.19 (GP9)
DOME_INB: J3.8 (INB2), R23.1, U2.20 (GP10)
DOME_PWM: J3.4 (PWM2), R21.1, U2.18 (GP8)
DRIVE_INA: J2.5 (INA1), R13.1, U1.25 (RX2)
DRIVE_INB: J2.7 (INB1), R14.1, U1.24 (TX2)
DRIVE_PWM: J2.3 (PWM1), R12.1, U1.26 (D4)
ENC_A_3V3: U2.21 (GP11), U7.18 (B1)
ENC_A_5V: J8.3 (A), U7.2 (A1)
ENC_B_3V3: U2.22 (GP12), U7.17 (B2)
ENC_B_5V: J8.4 (B), U7.3 (A2)
ESTOP_SENSE: J15.1 (LOOP), R28.2, U1.2 (VP)
FLY_INA: J3.5 (INA1), R19.1, U1.7 (D33)
FLY_INB: J3.7 (INB1), R20.1, U1.11 (D14)
FLY_PWM: J3.3 (PWM1), R18.1, U1.6 (D32)
GND: C1.2, C2.2, C3.2, C4.2, C5.2, C6.2, C7.2, C8.2, C9.2, C10.2, C11.2, C12.2, C28.2, D1.2, H1.1, H2.1, H3.1, H4.1, H5.1, J1.2 (-), J2.9 (GND), J2.10 (GND), J3.9 (GND), J3.10 (GND), J4.3 (GND), J5.3 (GND), J6.2 (GND), J7.2 (GND), J8.2 (GND), J9.2 (GND), J10.2 (GND), J11.2 (GND), J15.2 (GND), J16.1 (GND), J17.1 (GND), J_AMP.2 (GND), J_AMP.5 (AGND), PS1.2 (GND), PS2.2 (GND), Q1.3 (G), R12.2, R13.2, R14.2, R15.2, R16.2, R17.2, R18.2, R19.2, R20.2, R21.2, R22.2, R23.2, R25.2, R27.2, R30.2, U1.14 (GND), U1.29 (GND), U2.2 (GND), U3.7 (GND), U3.10 (GND), U5.1 (GND), U6.1 (1OE), U6.4 (2OE), U6.5 (2A), U6.7 (GND), U6.9 (3A), U6.10 (3OE), U6.12 (4A), U6.13 (4OE), U7.1 (DIR), U7.10 (GND), U7.19 (OE)
HALL: J9.3 (SIG), R9.2, U2.23 (GP13)
I2C_A_SCL: J7.5 (SCL), J16.4 (SCL), R6.2, U1.28 (D15)
I2C_A_SDA: J7.4 (SDA), J16.3 (SDA), R5.2, U1.13 (D13)
I2C_B_SCL: J17.4 (SCL), J_AMP.7 (SCL), R8.2, U2.6 (GP27)
I2C_B_SDA: J17.3 (SDA), J_AMP.6 (SDA), R7.2, U2.7 (GP26)
IMU_CS: J6.6 (CS), U1.23 (D5)
IMU_MISO: J6.4 (MISO), U1.21 (D19)
IMU_MOSI: R32.1, U1.16 (D23)
IMU_MOSI_R: J6.5 (MOSI), R32.2
IMU_SCK: R31.1, U1.22 (D18)
IMU_SCK_R: J6.3 (SCK), R31.2
LINK_ESP_TX: U1.20 (D21), U2.11 (GP1)
LINK_RP_TX: U1.17 (D22), U2.10 (GP0)
NEO_3V3: U2.9 (GP14), U6.2 (1A)
NEO_5V: R3.1, U6.3 (1Y)
NEO_OUT: J10.3 (DATA), R3.2
RP_5V: C12.1, D2.2, U2.1 (5V)
S2S_INA: J2.6 (INA2), R16.1, U1.9 (D26)
S2S_INB: J2.8 (INB2), R17.1, U1.10 (D27)
S2S_OUT: J7.3 (OUT), R2.1
S2S_POS: C28.1, R2.2, U1.4 (D34)
S2S_PWM: J2.4 (PWM2), R15.1, U1.8 (D25)
SERVO_L: J4.1 (SIG), U2.16 (GP6)
SERVO_R: J5.1 (SIG), U2.17 (GP7)
SPK_L+: J13.1 (+), J_AMP.9 (OUTL+)
SPK_L-: J13.2 (-), J_AMP.10 (OUTL-)
SPK_R+: J14.1 (+), J_AMP.11 (OUTR+)
SPK_R-: J14.2 (-), J_AMP.12 (OUTR-)
V5_SENSE: R29.2, R30.1, U2.5 (GP28)
VBAT_SENSE: R24.2, R25.1, U1.5 (D35)
VIN: C1.1, D1.1, F4.1, PS1.1 (VIN), PS2.1 (VIN), Q1.2 (D), R24.1
